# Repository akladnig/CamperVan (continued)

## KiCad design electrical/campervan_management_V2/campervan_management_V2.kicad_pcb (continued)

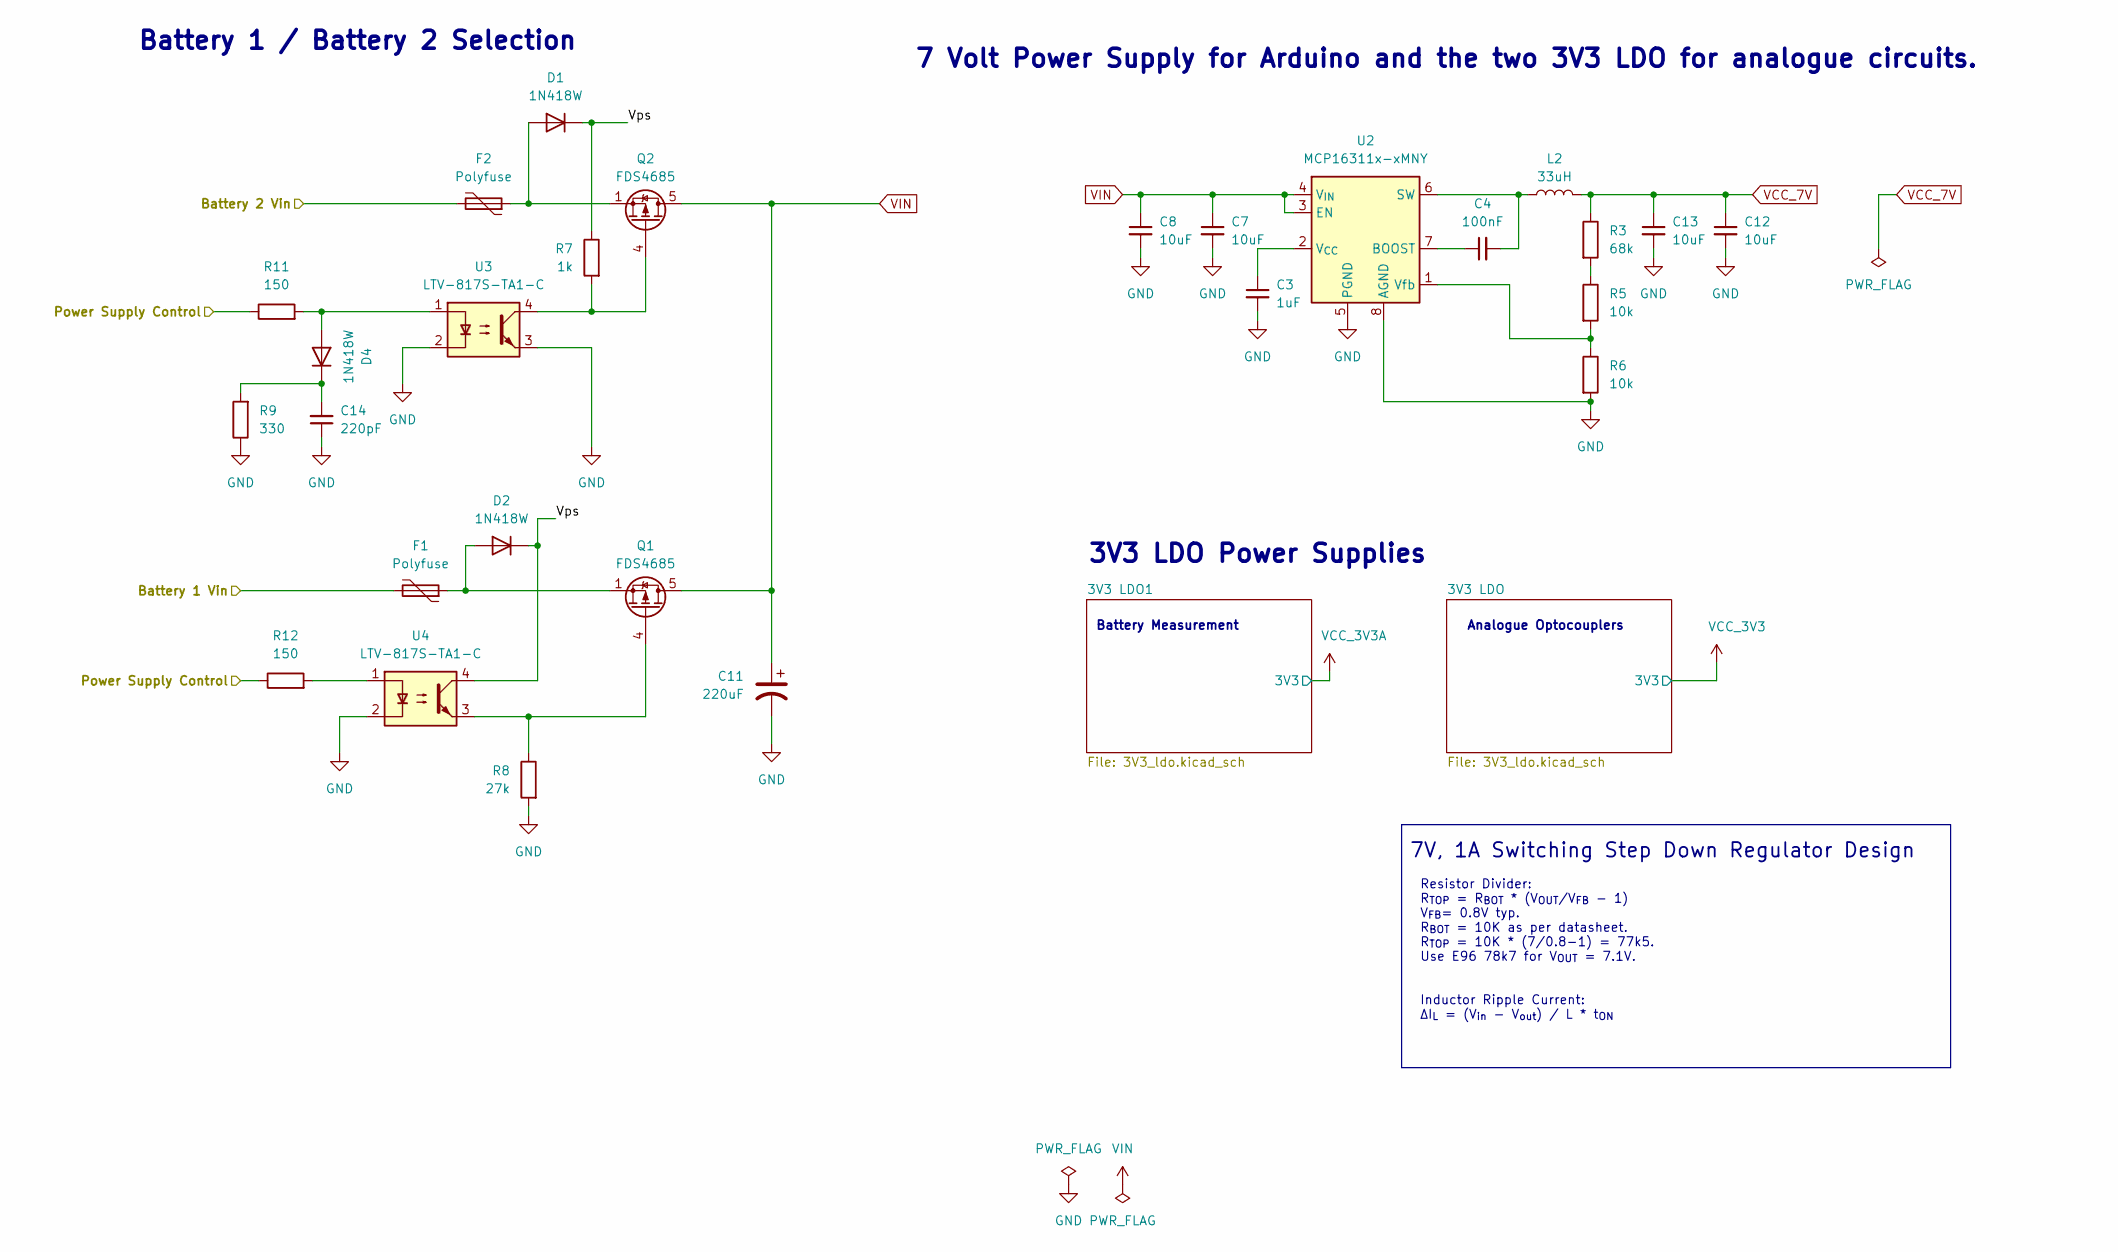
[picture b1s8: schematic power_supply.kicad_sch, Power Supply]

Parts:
C3: 1uF; C_0603_1608Metric; LCSC PN C15849
C4: 100nF; C_0805_2012Metric; LCSC PN C28233
C7, C8, C12, C13: 10uF; C_1206_3216Metric; LCSC PN C13585
C11: 220uF; C_Radial_D6.3mm_H11.0mm_P2.50mm
C14: 220pF; C_0805_2012Metric; LCSC PN C28233
D1, D2, D4: 1N418W; D_SOD-123; LCSC PN C81598
F1, F2: Polyfuse; Fuse_1812_4532Metric
L2: 33uH; L_Coilcraft_MSS1038-XXX; LCSC PN C19191679
Q1, Q2: FDS4685; SOIC-8_3.9x4.9mm_P1.27mm; LCSC PN C336026
R3: 68k; R_0603_1608Metric; LCSC PN C23231
R5, R6: 10k; R_0603_1608Metric; LCSC PN C25804
R7: 1k; R_0805_2012Metric; LCSC PN C17713
R8: 27k; R_0805_2012Metric; LCSC PN C17713
R9: 330; R_0805_2012Metric; LCSC PN C17471
R11, R12: 150; R_0805_2012Metric; LCSC PN C17471
U2: MCP16311x-xMNY; DFN-8-1EP_3x2mm_P0.5mm_EP1.75x1.45mm; LCSC PN C510882
U3, U4: LTV-817S-TA1-C; SO-4_4.4x3.6mm_P2.54mm; LCSC PN C109227

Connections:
/Battery Voltage Measurement/Battery 1 Vin: F2.2; also elsewhere on the board
/Battery Voltage Measurement/Battery 2 Vin: F1.2; also elsewhere on the board
/Power Supply Control: R11.1, R12.1; also elsewhere on the board
/Power Supply/Vps: D1.1 (K), D2.1 (K), R7.1, U4.4
GND: C3.2, C7.2, C8.2, C11.2, C12.2, C13.2, C14.1, R6.2, R8.2, R9.1, U2.5 (PGND), U2.8 (AGND), U2.9 (GND), U3.2, U3.3, U4.2; also elsewhere on the board
unnamed: D1.2 (A), F2.1, Q2.1 (S), Q2.2 (S), Q2.3 (S)
unnamed: D2.2 (A), F1.1, Q1.1 (S), Q1.2 (S), Q1.3 (S)
unnamed: D4.2 (A), R11.2, U3.1
unnamed: C14.2, D4.1 (K), R9.2
unnamed: Q1.4 (G), R8.1, U4.3
unnamed: Q2.4 (G), R7.2, U3.4
unnamed: R3.2, R5.1
unnamed: R12.2, U4.1
unnamed: C4.1, U2.7 (BOOST)
unnamed: C4.2, L2.1, U2.6 (SW)
unnamed: C3.1, U2.2 (V_{CC})
unnamed: R5.2, R6.1, U2.1 (Vfb)
VCC_7V: C12.1, C13.1, L2.2, R3.1; also elsewhere on the board
VIN: C7.1, C8.1, C11.1, Q1.5 (D), Q1.6 (D), Q1.7 (D), Q1.8 (D), Q2.5 (D), Q2.6 (D), Q2.7 (D), Q2.8 (D), U2.3 (EN), U2.4 (V_{IN}); also elsewhere on the board

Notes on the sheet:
7V, 1A Switching Step Down Regulator Design
Battery Measurement
Resistor Divider: R_{TOP} = R_{BOT} * (V_{OUT}/V_{FB} - 1) V_{FB}= 0.8V typ. R_{BOT} = 10K as per datasheet. R_{TOP} = 10K * (7/0.8-1) = 77k5. Use E96 78k7 for V_{OUT} = 7.1V. Inductor Ripple Current: ∆I_{L} = (V_{in} - V_{out}) / L * t_{ON}
3V3 LDO Power Supplies
Analogue Optocouplers
Battery 1 / Battery 2 Selection
7 Volt Power Supply for Arduino and the two 3V3 LDO for analogue circuits.

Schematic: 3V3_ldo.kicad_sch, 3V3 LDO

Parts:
C15: 1uF; C_0603_1608Metric; LCSC PN C15849
C17, C18: 10uF; CP_EIA-3216-18_Kemet-A; LCSC PN C7171
U5: AMS1117-3.3/TLV761; SOT-223-3_TabPin2; LCSC PN C6186

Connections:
GND: C15.2, C17.2, C18.2, U5.1 (GND); also elsewhere on the board
VCC_3V3: C17.1, C18.1, U5.2 (VO); also elsewhere on the board
VCC_7V: C15.1, U5.3 (VI); also elsewhere on the board

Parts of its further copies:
C36: 1uF; C_0603_1608Metric; LCSC PN C15849
C37, C38: 10uF; CP_EIA-3216-18_Kemet-A; LCSC PN C7171
U22: AMS1117-3.3/TLV761; SOT-223-3_TabPin2; LCSC PN C6186

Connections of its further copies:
GND: C36.2, C37.2, C38.2, U22.1 (GND); also elsewhere on the board
VCC_3V3A: C37.1, C38.1, U22.2 (VO); also elsewhere on the board
VCC_7V: C36.1, U22.3 (VI); also elsewhere on the board

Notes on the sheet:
3V3 LDO One is used to power the battery voltage measurement. The second for all other 3V3 devices.

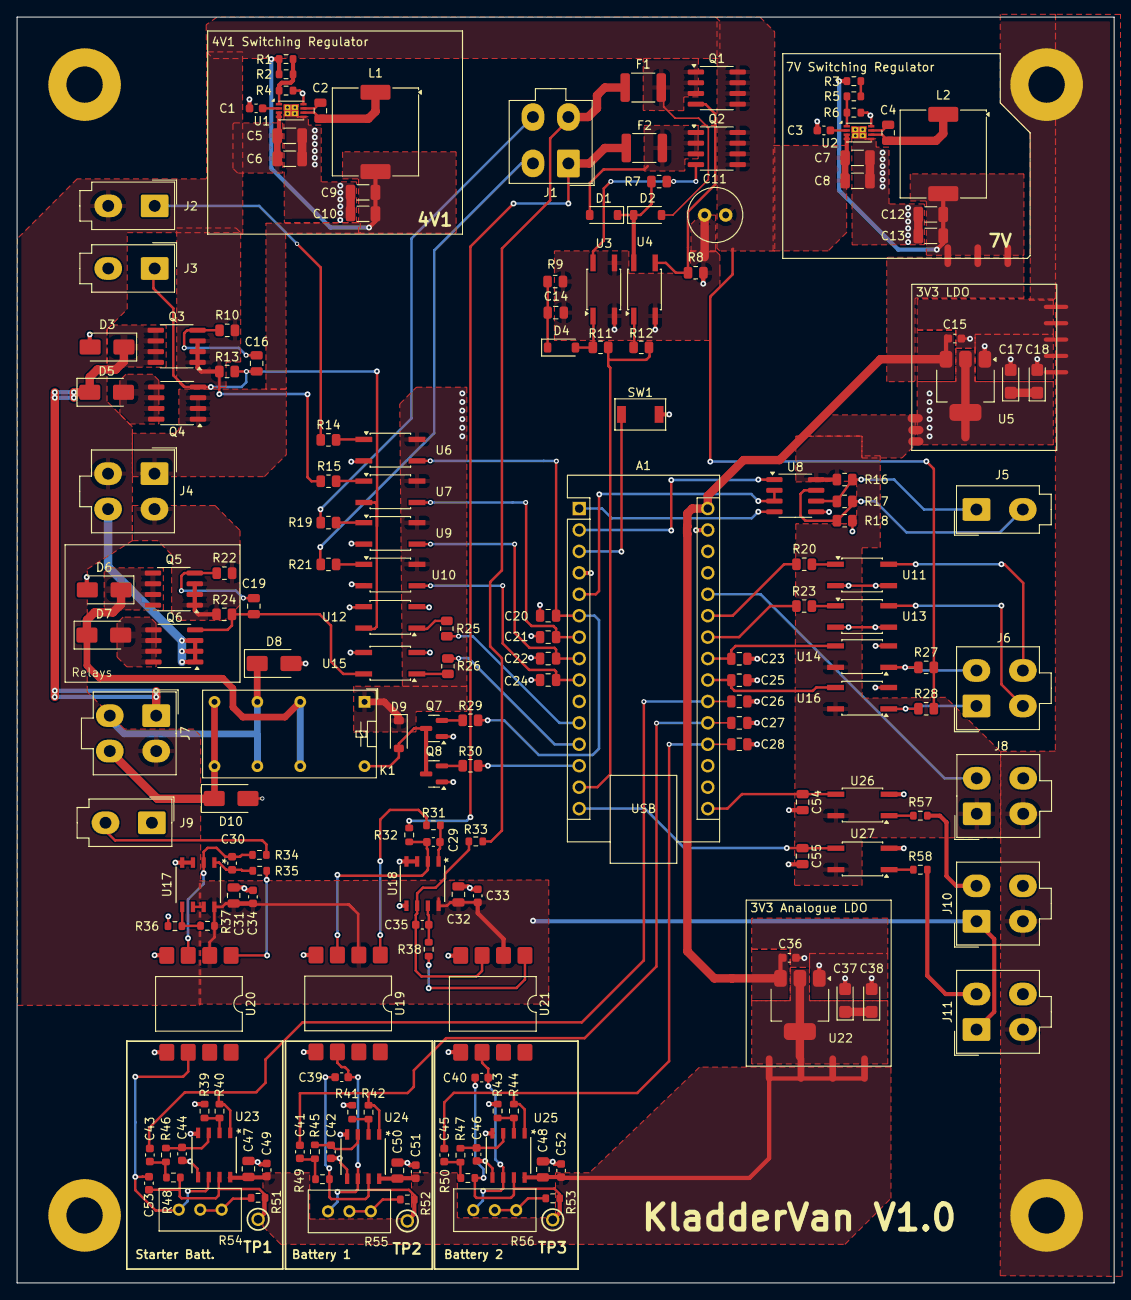
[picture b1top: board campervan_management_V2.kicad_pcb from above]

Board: 4 copper layers, 130.0 x 150.0 mm, 183 parts (0 on the bottom side), 113 nets.

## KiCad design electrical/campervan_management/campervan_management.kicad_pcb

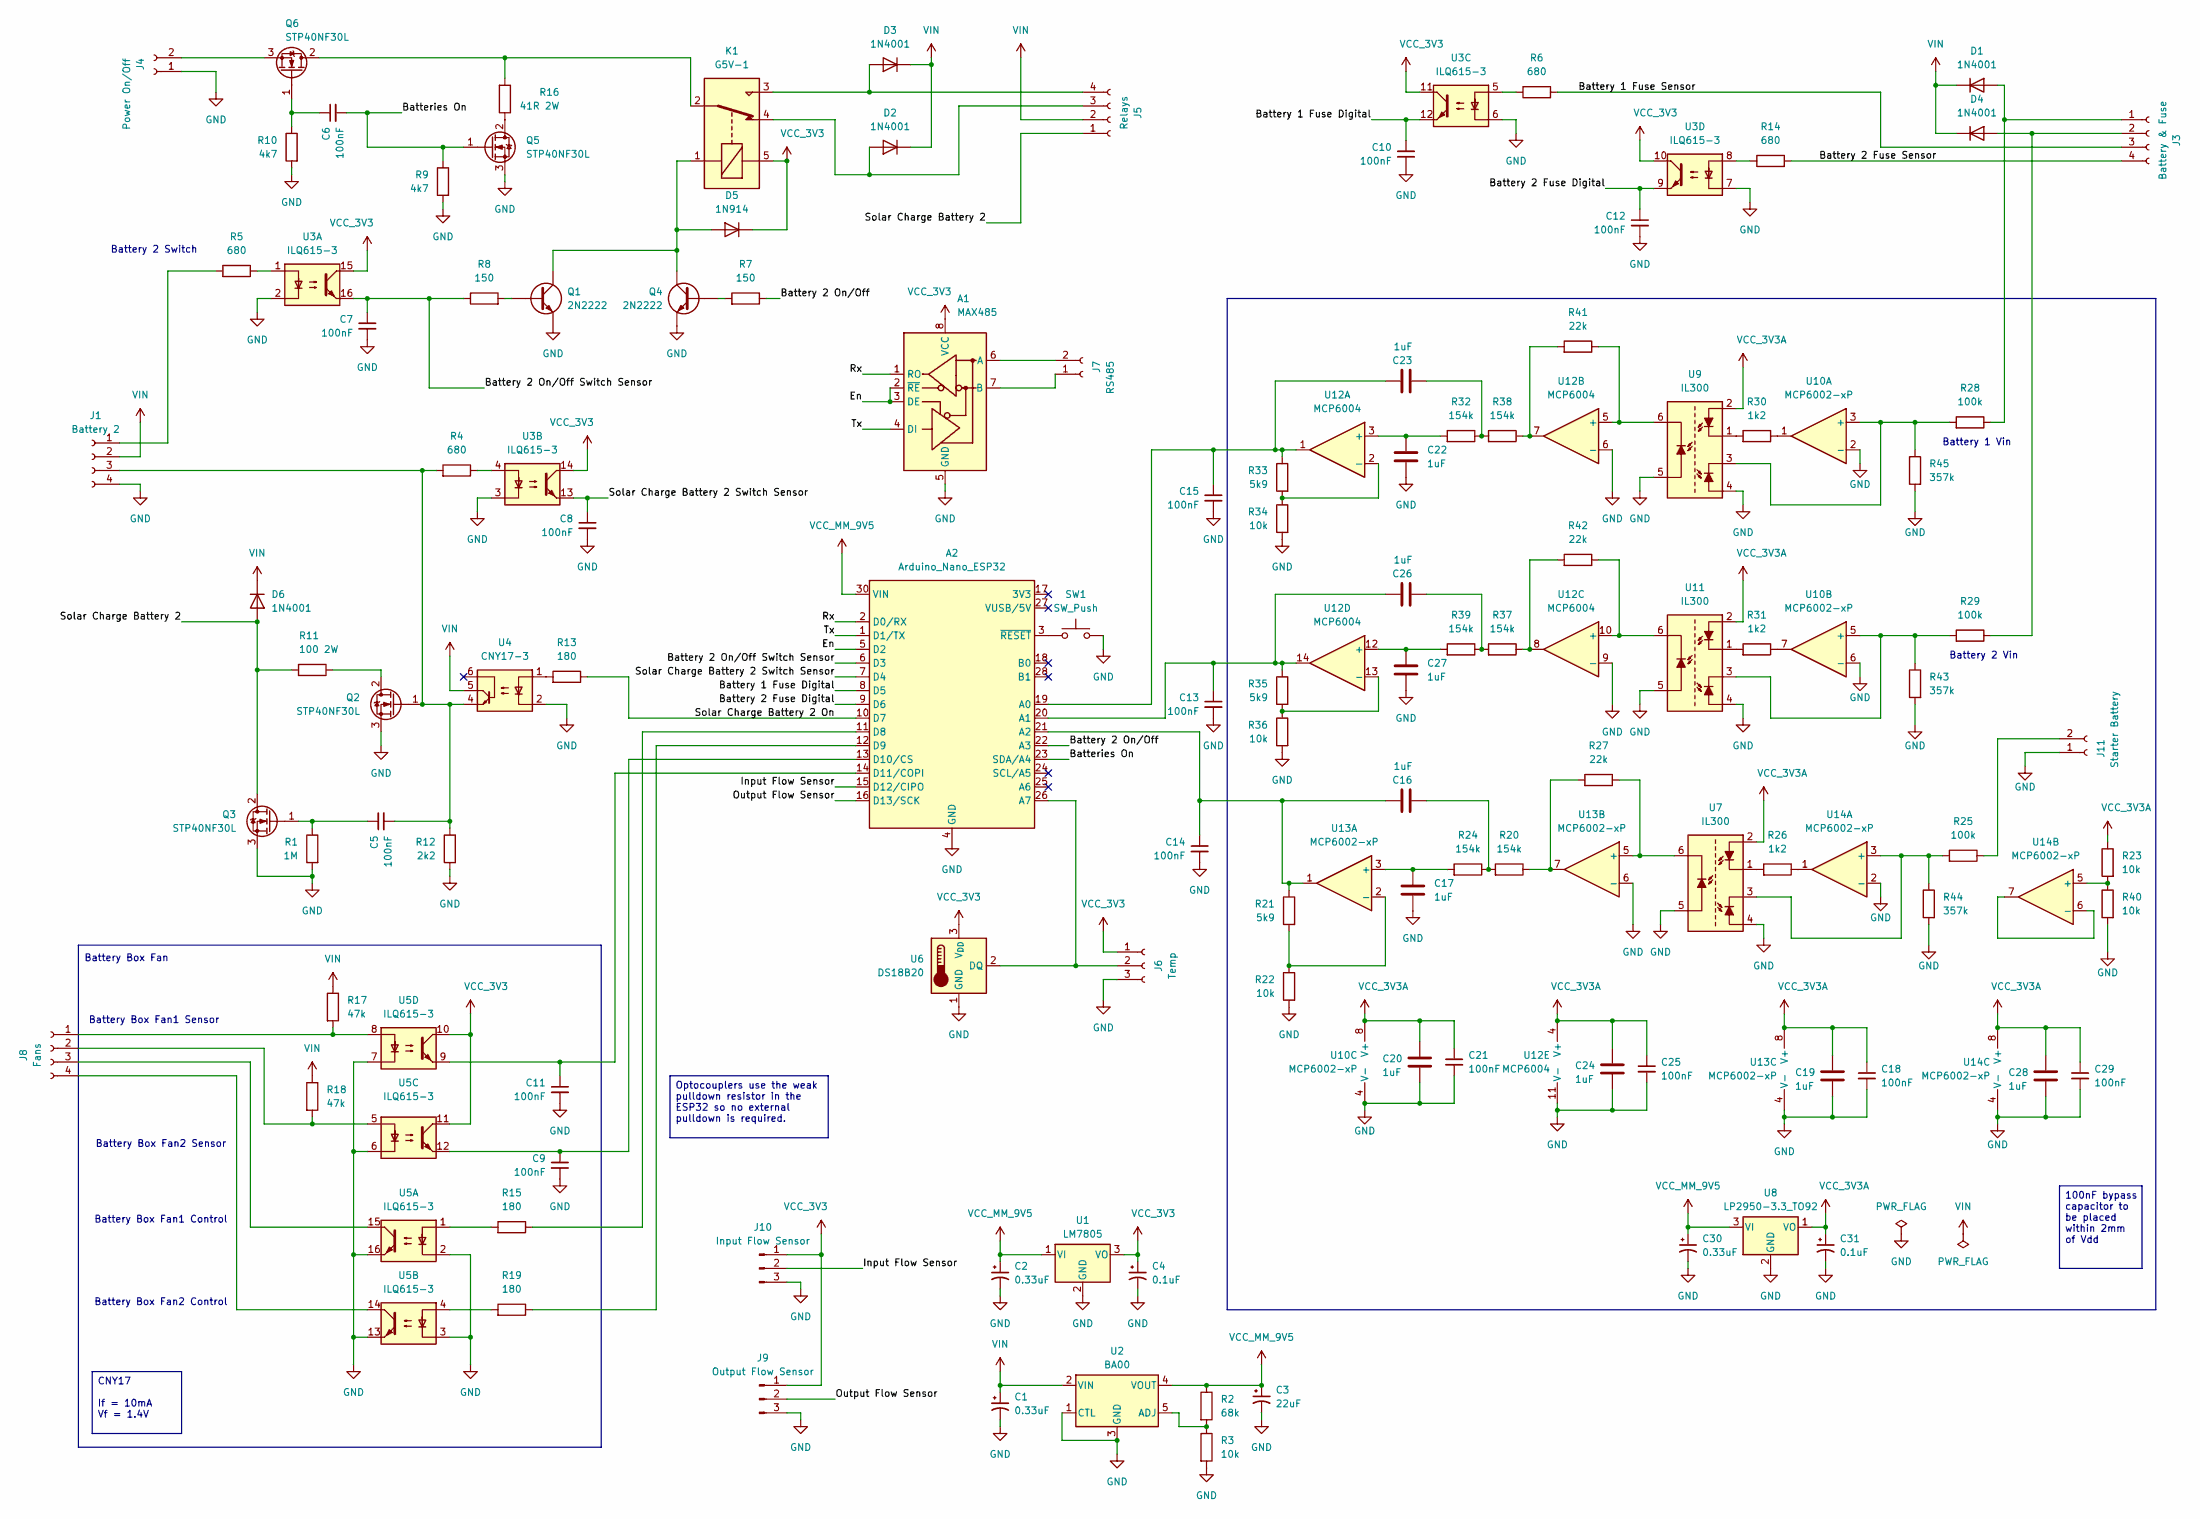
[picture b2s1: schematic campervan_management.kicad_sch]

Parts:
A1: MAX485; RS485_MODULE
A2: Arduino_Nano_ESP32; Arduino_Nano
C1, C2, C30: 0.33uF; C_Disc_D5.0mm_W2.5mm_P2.50mm
C3: 22uF; CP_Radial_Tantal_D4.5mm_P2.50mm
C4, C31: 0.1uF; CP_Radial_Tantal_D5.0mm_P5.00mm
C5, C6, C7, C8, C9, C10, C11, C12, C13, C14, C15, C18, C21, C25, C29: 100nF; C_Disc_D3.8mm_W2.6mm_P2.50mm
C16, C17, C19, C20, C22, C23, C24, C26, C27, C28: 1uF; CAP_NP_5X11_MTC
D1, D2, D3, D4, D6: 1N4001; D_DO-41_SOD81_P10.16mm_Horizontal
D5: 1N914; D_DO-35_SOD27_P7.62mm_Horizontal
J1: Battery 2; Molex_Mini-Fit_Jr_5566-04A_2x02_P4.20mm_Vertical
J3: Battery & Fuse; Molex_Mini-Fit_Jr_5566-04A_2x02_P4.20mm_Vertical
J4: Power On/Off; Molex_Mini-Fit_Jr_5566-02A_2x01_P4.20mm_Vertical
J5: Relays; Molex_Mini-Fit_Jr_5566-04A_2x02_P4.20mm_Vertical
J6: Temp; PinSocket_1x03_P2.54mm_Vertical
J7: RS485; Molex_Mini-Fit_Jr_5566-02A_2x01_P4.20mm_Vertical
J8: Fans; Molex_Mini-Fit_Jr_5566-04A_2x02_P4.20mm_Vertical
J9: Output Flow Sensor; PinSocket_1x03_P2.54mm_Vertical
J10: Input Flow Sensor; PinSocket_1x03_P2.54mm_Vertical
J11: Starter Battery; Molex_Mini-Fit_Jr_5566-02A_2x01_P4.20mm_Vertical
K1: G5V-1; Relay_SPDT_Omron-G5Q-1
Q1, Q4: 2N2222; TO-18-3
Q2, Q3, Q5, Q6: STP40NF30L; TO-220F-3_Vertical
R1: 1M; R_Axial_DIN0207_L6.3mm_D2.5mm_P10.16mm_Horizontal
R2: 68k; R_Axial_DIN0207_L6.3mm_D2.5mm_P10.16mm_Horizontal
R3, R22, R23, R34, R36, R40: 10k; R_Axial_DIN0207_L6.3mm_D2.5mm_P10.16mm_Horizontal
R4, R5, R6, R14: 680; R_Axial_DIN0207_L6.3mm_D2.5mm_P10.16mm_Horizontal
R7, R8: 150; R_Axial_DIN0207_L6.3mm_D2.5mm_P10.16mm_Horizontal
R9, R10: 4k7; R_Axial_DIN0207_L6.3mm_D2.5mm_P10.16mm_Horizontal
R11: 100 2W; R_Axial_DIN0414_L11.9mm_D4.5mm_P25.40mm_Horizontal
R12: 2k2; R_Axial_DIN0207_L6.3mm_D2.5mm_P10.16mm_Horizontal
R13, R15, R19: 180; R_Axial_DIN0207_L6.3mm_D2.5mm_P10.16mm_Horizontal
R16: 41R 2W; R_Axial_DIN0414_L11.9mm_D4.5mm_P25.40mm_Horizontal
R17, R18: 47k; R_Axial_DIN0207_L6.3mm_D2.5mm_P10.16mm_Horizontal
R20, R24, R32, R37, R38, R39: 154k; R_Axial_DIN0207_L6.3mm_D2.5mm_P10.16mm_Horizontal
R21, R33, R35: 5k9; R_Axial_DIN0207_L6.3mm_D2.5mm_P10.16mm_Horizontal
R25, R28, R29: 100k; R_Axial_DIN0207_L6.3mm_D2.5mm_P10.16mm_Horizontal
R26, R30, R31: 1k2; R_Axial_DIN0207_L6.3mm_D2.5mm_P10.16mm_Horizontal
R27, R41, R42: 22k; R_Axial_DIN0207_L6.3mm_D2.5mm_P10.16mm_Horizontal
R43, R44, R45: 357k; R_Axial_DIN0207_L6.3mm_D2.5mm_P10.16mm_Horizontal
SW1: SW_Push; SW_TH_Tactile_Omron_B3F-102x
U1: LM7805; TO-220-3_Vertical
U2: BA00; TO-220-5_P3.4x3.8mm_StaggerOdd_Lead7.13mm_TabDown
U3, U5: ILQ615-3; DIP-16_W7.62mm
U4: CNY17-3; DIP-6_W7.62mm
U6: DS18B20; TO-92_Inline
U7, U9, U11: IL300; DIP-8_W7.62mm
U8: LP2950-3.3_TO92; TO-92_Inline
U10, U13, U14: MCP6002-xP; DIP-8_W7.62mm
U12: MCP6004; DIP-14_W7.62mm

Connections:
/Batteries On: A2.23 (SDA/A4), C6.2, Q5.1 (G), R9.1
/Battery 1 Fuse Digital: A2.8 (D5), C10.1, U3.12
/Battery 1 Fuse Sensor: J3.3, R6.2
/Battery 2 Fuse Digital: A2.9 (D6), C12.1, U3.9
/Battery 2 Fuse Sensor: J3.4, R14.2
/Battery 2 On/Off: A2.22 (A3), R7.1
/Battery 2 On/Off Switch Sensor: A2.6 (D3), C7.1, R8.1, U3.16
/En: A1.2 (~RE), A1.3 (DE), A2.5 (D2)
/Input Flow Sensor: A2.15 (D12/CIPO), J10.2
/Output Flow Sensor: A2.16 (D13/SCK), J9.2
/Rx: A1.1 (RO), A2.2 (D0/RX)
/Solar Charge Battery 2: D6.2 (A), J5.1, Q3.2 (D), R11.2
/Solar Charge Battery 2 On: A2.10 (D7), R13.1
/Solar Charge Battery 2 Switch Sensor: A2.7 (D4), C8.1, U3.13
/Tx: A1.4 (DI), A2.1 (D1/TX)
GND: A1.5 (GND), A2.4 (GND), A2.29 (GND), C1.2, C2.2, C3.2, C4.2, C7.2, C8.2, C9.2, C10.2, C11.2, C12.2, C13.2, C14.2, C15.2, C17.2, C18.2, C19.2, C20.2, C21.2, C22.2, C24.2, C25.2, C27.2, C28.2, C29.2, C30.2, C31.2, J1.4, J4.1, J6.3, J9.3, J10.3, J11.1, Q1.1 (E), Q2.3 (S), Q3.3 (S), Q4.1 (E), Q5.3 (S), R1.2, R3.2, R9.2, R10.2, R12.2, R22.2, R34.2, R36.2, R40.2, R43.2, R44.2, R45.2, SW1.2, U1.2 (GND), U2.1 (CTL), U2.3 (GND), U3.2, U3.3, U3.6, U3.7, U4.2, U5.2, U5.3, U5.6, U5.7, U5.13, U5.16, U6.1 (GND), U7.4, U7.5, U8.2 (GND), U9.4, U9.5, U10.2 (-), U10.4 (V-), U10.6 (-), U11.4, U11.5, U12.6 (-), U12.9 (-), U12.11 (V-), U13.4 (V-), U13.6 (-), U14.2 (-), U14.4 (V-)
unnamed: A1.6 (A), J7.2
unnamed: A1.7 (B), J7.1
unnamed: A2.19 (A0), C15.1, C23.2, R33.1, U12.1
unnamed: A2.20 (A1), C13.1, C26.2, R35.1, U12.14
unnamed: A2.21 (A2), C14.1, C16.2, R21.1, U13.1
unnamed: A2.26 (A7), J6.2, U6.2 (DQ)
unnamed: A2.11 (D8), R15.1
unnamed: A2.12 (D9), R19.1
unnamed: A2.13 (D10/CS), C9.1, U5.12
unnamed: A2.14 (D11/COPI), C11.1, U5.9
unnamed: A2.3 (~RESET), SW1.1
unnamed: C16.1, R20.2, R24.1
unnamed: C23.1, R32.1, R38.2
unnamed: C26.1, R37.2, R39.1
unnamed: D1.2 (A), J3.1, R28.1
unnamed: D2.2 (A), J5.3, K1.4
unnamed: D3.2 (A), J5.4, K1.3
unnamed: D4.2 (A), J3.2, R29.1
unnamed: D5.2 (A), K1.1, Q1.3 (C), Q4.3 (C)
unnamed: J1.1, R5.2
unnamed: C5.2, J1.3, Q2.1 (G), R4.2, R12.1, U4.4
unnamed: J4.2, Q6.3 (S)
unnamed: J8.1, R17.2, U5.8
unnamed: J8.2, R18.2, U5.5
unnamed: J8.3, U5.15
unnamed: J8.4, U5.14
unnamed: J11.2, R25.1
unnamed: Q1.2 (B), R8.2
unnamed: Q2.2 (D), R11.1
unnamed: C5.1, Q3.1 (G), R1.1
unnamed: Q4.2 (B), R7.2
unnamed: Q5.2 (D), R16.1
unnamed: K1.2, Q6.2 (D), R16.2
unnamed: C6.1, Q6.1 (G), R10.1
unnamed: R4.1, U3.4
unnamed: R5.1, U3.1
unnamed: R6.1, U3.5
unnamed: R13.2, U4.1
unnamed: R14.1, U3.8
unnamed: R15.2, U5.1
unnamed: R19.2, U5.4
unnamed: R20.1, R27.2, U13.7
unnamed: R26.1, U14.1
unnamed: R26.2, U7.1
unnamed: R30.1, U10.1
unnamed: R30.2, U9.1
unnamed: R31.1, U10.7
unnamed: R31.2, U11.1
unnamed: R37.1, R42.2, U12.8
unnamed: R38.1, R41.2, U12.7
unnamed: R2.2, R3.1, U2.5 (ADJ)
unnamed: R28.2, R45.1, U9.3, U10.3 (+)
unnamed: R29.2, R43.1, U10.5 (+), U11.3
unnamed: C22.1, R32.2, U12.3 (+)
unnamed: R33.2, R34.1, U12.2 (-)
unnamed: R41.1, U9.6, U12.5 (+)
unnamed: R42.1, U11.6, U12.10 (+)
unnamed: C27.1, R39.2, U12.12 (+)
unnamed: R35.2, R36.1, U12.13 (-)
unnamed: C17.1, R24.2, U13.3 (+)
unnamed: R21.2, R22.1, U13.2 (-)
unnamed: R27.1, U7.6, U13.5 (+)
unnamed: R25.2, R44.1, U7.3, U14.3 (+)
unnamed: R23.2, R40.1, U14.5 (+)
unnamed: U14.6 (-), U14.7
VCC_3V3: A1.8 (VCC), C4.1, D5.1 (K), J6.1, J9.1, J10.1, K1.5, U1.3 (VO), U3.10, U3.11, U3.14, U3.15, U5.10, U5.11, U6.3 (V_{DD})
VCC_3V3A: C18.1, C19.1, C20.1, C21.1, C24.1, C25.1, C28.1, C29.1, C31.1, R23.1, U7.2, U8.1 (VO), U9.2, U10.8 (V+), U11.2, U12.4 (V+), U13.8 (V+), U14.8 (V+)
VCC_MM_9V5: A2.30 (VIN), C2.1, C3.1, C30.1, R2.1, U1.1 (VI), U2.4 (VOUT), U8.3 (VI)
VIN: C1.1, D1.1 (K), D2.1 (K), D3.1 (K), D4.1 (K), D6.1 (K), J1.2, J5.2, R17.1, R18.1, U2.2 (VIN), U4.5

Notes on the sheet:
Battery Box Fan
Battery 2 Switch
Battery Box Fan1 Control
Battery 2 Vin
Battery Box Fan1 Sensor
Battery Box Fan2 Sensor
Battery Box Fan2 Control
Battery 1 Vin
Optocouplers use the weak pulldown resistor in the ESP32 so no external pulldown is required.
CNY17 If = 10mA Vf = 1.4V
100nF bypass capacitor to be placed within 2mm of Vdd

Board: 2 copper layers, 116 parts (0 on the bottom side), 85 nets, no tracks yet.

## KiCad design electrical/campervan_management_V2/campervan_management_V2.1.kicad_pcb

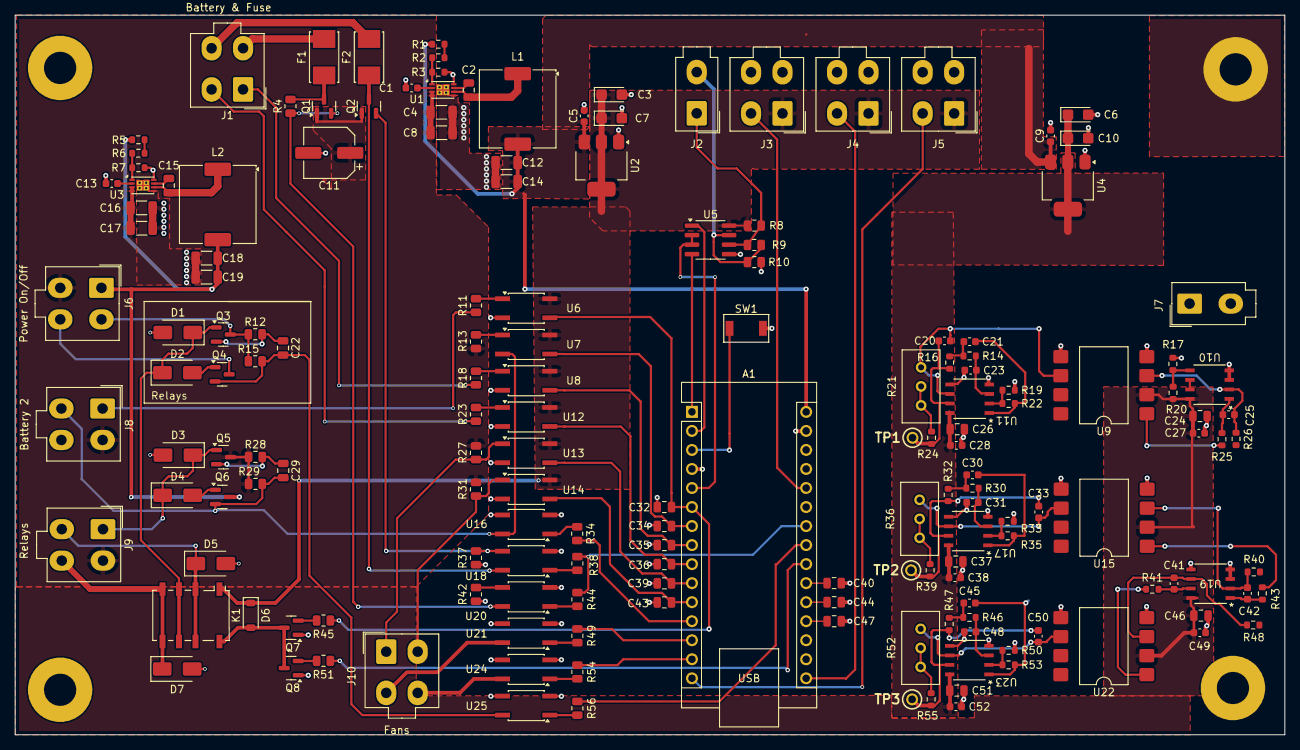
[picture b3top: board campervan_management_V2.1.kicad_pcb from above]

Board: 4 copper layers, 169.5 x 96.0 mm, 172 parts (0 on the bottom side), 109 nets.

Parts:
A1: Arduino_Nano_ESP32; Arduino_Nano
C1, C5, C9, C13, C21, C23, C27, C28, C30, C31, C38, C45, C48, C49, C52: 1uF; C_0603_1608Metric
C2, C15, C22, C24, C26, C29, C32, C34, C35, C36, C37, C39, C40, C43, C44, C46, C47, C51: 100nF; C_0805_2012Metric
C3, C6, C7, C10: 10uF; CP_EIA-3216-18_Kemet-A
C4, C8, C12, C14, C16, C17, C18, C19: 10uF; C_1206_3216Metric
C11: 220uF; CP_Elec_6.3x5.9
C20, C25, C33, C41, C42, C50: C_Small; C_0603_1608Metric
D1, D2, D3, D4, D5, D7: M7; D_SMA
D6: 1N418W; D_SOD-123
F1, F2: Polyfuse; Fuseholder_Littelfuse_Nano2_157x
H1, H2, H3, H4: MountingHole_Pad; MountingHole_4.3mm_M4_Pad
J1: Battery & Fuse; Molex_Mini-Fit_Jr_5566-04A_2x02_P4.20mm_Vertical
J2: RS485; Molex_Mini-Fit_Jr_5566-02A_2x01_P4.20mm_Vertical
J3: Temp; Molex_Mini-Fit_Jr_5566-04A_2x02_P4.20mm_Vertical
J4: Output Flow Sensor; Molex_Mini-Fit_Jr_5566-04A_2x02_P4.20mm_Vertical
J5: Input Flow Sensor; Molex_Mini-Fit_Jr_5566-04A_2x02_P4.20mm_Vertical
J6: Power On/Off Switch; Molex_Mini-Fit_Jr_5566-04A_2x02_P4.20mm_Vertical
J7: Starter Battery; Molex_Mini-Fit_Jr_5566-02A_2x01_P4.20mm_Vertical
J8: Battery 2; Molex_Mini-Fit_Jr_5566-04A_2x02_P4.20mm_Vertical
J9: Relays; Molex_Mini-Fit_Jr_5566-04A_2x02_P4.20mm_Vertical
J10: Fans; Molex_Mini-Fit_Jr_5566-04A_2x02_P4.20mm_Vertical
K1: G6KU-2; Relay_DPDT_Omron_G6K-2F-Y
L1: 33uH; L_Coilcraft_MSS1038-XXX
L2: 18uH; L_Coilcraft_MSS1038-XXX
Q1, Q2, Q3, Q4, Q5, Q6: Q_PMOS_DGS; SOT-23
Q7, Q8: MMBT2222A; SOT-23
R1, R5: 68k; R_0603_1608Metric
R2, R3, R6, R7, R17, R19, R20, R33, R50: 10k; R_0603_1608Metric
R4, R15, R27, R29, R31, R37, R42: 47k; R_0805_2012Metric
R8, R10: 931; R_0805_2012Metric
R9: 120; R_0805_2012Metric
R11, R13, R18, R23: 680; R_0805_2012Metric
R12, R28: 1M; R_0805_2012Metric
R14, R16, R30, R32, R46, R47: 150k; R_0603_1608Metric
R21, R36, R52: 10k; Potentiometer_Bourns_3296W_Vertical
R22, R35, R53: 5k6; R_0603_1608Metric
R24, R39, R55: 22k; R_0603_1608Metric
R25, R41, R43: 1k2; R_0603_1608Metric
R26, R40, R48: 220k; R_0603_1608Metric
R34, R38, R44, R45, R49, R51, R54, R56: 150; R_0805_2012Metric
SW1: SW_Push; SW_SPST_JLC
TP1, TP2, TP3: TestPoint; 5000
U1, U3: MCP16311x-xMNY; DFN-8-1EP_3x2mm_P0.5mm_EP1.75x1.45mm
U2, U4: AMS1117-3.3; SOT-223-3_TabPin2
U5: MAX487E; SOIC-8_3.9x4.9mm_P1.27mm
U6, U7, U8, U12, U13, U14, U16, U18, U20, U21, U24, U25: LTV-817S-TA1-C; SO-4_4.4x3.6mm_P2.54mm
U9, U15, U22: HCNR200-500E; SMDIP-8_W11.48mm
U10, U11, U17, U19, U23: LM358DR2G; SOIC-8_ONS-L

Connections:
/Batteries On: A1.23 (SDA/A4), R56.1
/Battery 1 Fuse State: A1.8 (D5), C35.1, U8.3
/Battery 2 Fuse State: A1.9 (D6), C36.1, U12.3
/Battery 2 On/Off: A1.22 (A3), R51.1
/Battery 2 On/Off Switch Sensor: A1.6 (D3), C32.1, R45.1, U6.3
/Battery Box Fan1 Control: A1.13 (D10/CS), R49.1
/Battery Box Fan1 Sensor: A1.11 (D8), C43.1, U14.3
/Battery Box Fan2 Control: A1.14 (D11/COPI), R54.1
/Battery Box Fan2 Sensor: A1.10 (D7), C39.1, U13.3
/Battery Fuse Sensors/Battery 1 Fuse Sensor: J1.1, R18.2
/Battery Fuse Sensors/Battery 2 Fuse Sensor: J1.2, R23.2
/Battery Management/Battery 1 Relay: D7.1 (K), J9.4, K1.4, K1.5
/Battery Management/Battery 2 Relay: D5.1 (K), J9.3, K1.2, K1.7
/Battery Management/Battery 2 Switch: J8.1, R11.2
/Battery Management/Power On Switch - 4V1: J6.2, Q3.3 (S), R12.1, R15.1
/Battery Management/Power On Switch - Vin: J6.4, Q4.3 (S)
/Battery Voltage Measurement/Battery 1 Vin: F2.2, J1.4, R40.1
/Battery Voltage Measurement/Battery 1 Voltage: A1.20 (A1), C30.2, C44.1, R35.1, U17.1
/Battery Voltage Measurement/Battery 2 Vin: F1.2, J1.3, R48.1
/Battery Voltage Measurement/Battery 2 Voltage: A1.21 (A2), C40.1, C45.2, R53.1, U23.1
/Battery Voltage Measurement/Starter Battery Vin: J7.2, R26.1
/Battery Voltage Measurement/Starter Battery Voltage: A1.19 (A0), C21.2, C47.1, R22.1, U11.1
/En: A1.5 (D2), U5.2 (~RE), U5.3 (DE)
/Input Flow Sensor: A1.15 (D12/CIPO), J5.2
/Output Flow Sensor: A1.16 (D13/SCK), J4.2
/Power Supply Control: A1.24 (SCL/A5), R38.1, R44.1
/Rx: A1.2 (D0/RX), U5.1 (RO)
/Solar Charge Battery 2 Relay: D3.1 (K), D4.1 (K), J9.1, Q5.1 (D)
/Solar Charge Management/Solar Charge Battery 2 On: A1.12 (D9), R34.1
/Solar Charge Management/Solar Charge Battery 2 Switch: C29.2, J8.3, Q6.2 (G), R29.2, U7.2, U16.4
/Solar Charge Management/Solar Charge Battery 2 Switch Sensor: A1.7 (D4), C34.1, U7.3
/Tx: A1.1 (D1/TX), U5.4 (DI)
GND: A1.4 (GND), A1.29 (GND), C1.2, C3.2, C4.2, C5.2, C6.2, C7.2, C8.2, C9.2, C10.2, C11.2, C12.2, C13.2, C14.2, C16.2, C17.2, C18.2, C19.2, C23.2, C24.2, C26.2, C27.2, C28.2, C31.2, C32.2, C34.2, C35.2, C36.2, C37.2, C38.2, C39.2, C40.2, C43.2, C44.2, C46.2, C47.2, C48.2, C49.2, C51.2, C52.2, D1.2 (A), D3.2 (A), D5.2 (A), D7.2 (A), H1.1, H2.1, H3.1, H4.1, J3.3, J4.3, J5.3, J7.1, J8.4, Q7.1 (E), Q8.1 (E), R3.2, R7.2, R10.2, R17.2, R19.2, R33.2, R37.2, R42.2, R50.2, SW1.2, U1.5 (PGND), U1.8 (AGND), U1.9 (GND), U2.1 (GND), U3.5 (PGND), U3.8 (AGND), U3.9 (GND), U4.1 (GND), U5.5 (GND), U6.2, U8.2, U9.4, U9.5, U10.3 (+), U10.4 (V-), U11.4 (V-), U11.5 (+), U12.2, U13.2, U14.2, U15.4, U15.5, U16.2, U16.3, U17.4 (V-), U17.5 (+), U18.2, U19.3 (+), U19.4 (V-), U19.5 (+), U20.2, U21.2, U21.3, U22.4, U22.5, U23.4 (V-), U23.5 (+), U24.2, U24.3, U25.2, U25.3
unnamed: A1.26 (A7), J3.2
unnamed: A1.3 (~RESET), SW1.1
unnamed: C25.1, R25.1, U10.1
unnamed: C20.1, R16.1, R24.2, TP1.1, U11.7
unnamed: C41.1, R41.1, U19.7
unnamed: C45.1, R46.1, R47.2
unnamed: C30.1, R30.1, R32.2
unnamed: C21.1, R14.1, R16.2
unnamed: C42.1, R43.1, U19.1
unnamed: C50.1, R47.1, R55.2, TP3.1, U23.7
unnamed: C33.1, R32.1, R39.2, TP2.1, U17.7
unnamed: D4.2 (A), Q6.1 (D)
unnamed: D2.2 (A), Q4.1 (D)
unnamed: D1.1 (K), D2.1 (K), K1.3, K1.6, Q3.1 (D)
unnamed: D6.2 (A), K1.8, Q7.3 (C), Q8.3 (C)
unnamed: J10.1, R27.2, U13.1
unnamed: J10.2, R31.2, U14.1
unnamed: J10.3, U21.4
unnamed: J10.4, U24.4
unnamed: J2.1, R8.2, R9.1, U5.6 (A)
unnamed: J2.2, R9.2, R10.1, U5.7 (B)
unnamed: C22.2, Q4.2 (G), R15.2, U25.4
unnamed: C22.1, Q3.2 (G), R12.2
unnamed: Q7.2 (B), R45.2
unnamed: Q8.2 (B), R51.2
unnamed: C29.1, Q5.2 (G), R28.2
unnamed: Q2.2 (G), R37.1, U18.3
unnamed: F2.1, Q2.3 (S), U18.4
unnamed: Q1.2 (G), R4.2, U20.4
unnamed: F1.1, Q1.3 (S), R4.1
unnamed: R1.2, R2.1
unnamed: R43.2, U15.1
unnamed: R41.2, U22.1
unnamed: R5.2, R6.1
unnamed: R52.1, R52.2, R55.1
unnamed: R34.2, U16.1
unnamed: R36.1, R36.2, R39.1
unnamed: R56.2, U25.1
unnamed: R13.2, U7.1
unnamed: R11.1, U6.1
unnamed: R25.2, U9.1
unnamed: R18.1, U8.1
unnamed: R21.1, R21.2, R24.1
unnamed: R23.1, U12.1
unnamed: R54.2, U24.1
unnamed: R49.2, U21.1
unnamed: R44.2, U20.1
unnamed: R42.1, U20.3
unnamed: R38.2, U18.1
unnamed: C2.1, U1.7 (BOOST)
unnamed: C2.2, L1.1, U1.6 (SW)
unnamed: C1.1, U1.2 (V_{CC})
unnamed: R2.2, R3.1, U1.1 (Vfb)
unnamed: C48.1, R46.2, U23.3 (+)
unnamed: R50.1, R53.2, U23.2 (-)
unnamed: C50.2, R52.3, U22.6, U23.6 (-)
unnamed: C42.2, R40.2, U15.3, U19.2 (-)
unnamed: C41.2, R48.2, U19.6 (-), U22.3
unnamed: C31.1, R30.2, U17.3 (+)
unnamed: R33.1, R35.2, U17.2 (-)
unnamed: C33.2, R36.3, U15.6, U17.6 (-)
unnamed: C25.2, R26.2, U9.3, U10.2 (-)
unnamed: R17.1, R20.2, U10.5 (+)
unnamed: U10.6 (-), U10.7
unnamed: C23.1, R14.2, U11.3 (+)
unnamed: R19.1, R22.2, U11.2 (-)
unnamed: C20.2, R21.3, U9.6, U11.6 (-)
unnamed: C15.1, U3.7 (BOOST)
unnamed: C15.2, L2.1, U3.6 (SW)
unnamed: C13.1, U3.2 (V_{CC})
unnamed: R6.2, R7.1, U3.1 (Vfb)
VCC_3V3: C3.1, C7.1, D6.1 (K), J3.1, J4.1, J5.1, K1.1, R8.1, U2.2 (VO), U5.8 (VCC), U6.4, U7.4, U8.4, U12.4, U13.4, U14.4
VCC_3V3A: C6.1, C10.1, C26.1, C28.1, C37.1, C38.1, C51.1, C52.1, U4.2 (VO), U11.8 (V+), U17.8 (V+), U23.8 (V+)
VCC_4V1: C18.1, C19.1, J6.1, L2.2, Q6.3 (S), R5.1
VCC_7V: A1.30 (VIN), C5.1, C9.1, C12.1, C14.1, L1.2, R1.1, U2.3 (VI), U4.3 (VI)
VIN: C4.1, C8.1, C11.1, C16.1, C17.1, C24.1, C27.1, C46.1, C49.1, J6.3, J8.2, J9.2, Q1.1 (D), Q2.1 (D), Q5.3 (S), R13.1, R20.1, R27.1, R28.1, R29.1, R31.1, U1.3 (EN), U1.4 (V_{IN}), U3.3 (EN), U3.4 (V_{IN}), U9.2, U10.8 (V+), U15.2, U19.8 (V+), U22.2

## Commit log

2025-04-06 second commit
2025-04-10 3rd commit
2025-04-16 4th commit
2025-04-16 Added design comments
2025-04-16 added schematic
2025-04-18 changed folder
2025-04-18 Added flow sensors and RS485
2025-04-18 updated electrical details
2025-04-18 removed RS485 TODO
2025-05-22 fix typos
2025-05-22 more typos!
2025-05-22 adjust size
2025-05-22 resize image
2025-05-22 fix formatting
2025-05-22 Updated TOC
2025-05-23 Design has been split into 3x modules
    - management module
    - fuse and switch modules
    - display module
2025-08-01 added infill to use wheelarch void
2025-08-01 added dimension for pop top
2025-08-01 added custom mattress size and increased size of headboaerd box to accomodate donna
2025-08-01 added handle to airfryer
2025-08-01 major updates to use a long box and changes to ducting
2025-08-01 changed water tank size and lowered bench height to allow window to be fitted
2025-08-01 added window, changed battery box, added parameter to show headboard box
2025-08-01 added pop top clearance and changed shelf height to support inverter
2025-08-01 added linear opto coupler design
2025-08-01 datasheets for selected components
2025-08-01 lots of redesign
2025-08-01 updated progress of todo
2025-08-01 changed benchheight to accomodate window
2025-08-01 added cupboard base panel
2025-08-01 formatting
2025-08-02 added showDimensions for draw front panels
2025-08-02 changed text size
2025-08-02 moved table design from cabinets to new file
2025-08-02 moved table design to new file
2025-08-02 changing clearances to see if sliding doors will work
2025-08-02 moved draw design to a separate file
2025-08-02 split cupboards into two separate modules
2025-08-03 split cupboards into modules and added openDrawsAndDoors parameter
2025-08-03 added openDoorsAndDraws parameter
2025-08-03 added function for angle of rear cupboard
2025-08-03 added sliding doors and door channels
2025-08-03 firxt commit
2025-08-03 Lots of updates - added 40mm duct and fans
2025-08-03 changed duct size
2025-08-03 added smaller duct size option
2025-08-03 updated fan calculations for thermal management
2025-08-21 work in progress
2025-08-29 First attempt at PCB design
2025-09-04 New SMD design
2025-09-04 Added footprints not in Kicad library
2025-09-04 Changed to high side relay drive and added 4.1V PS for high side relay hold
2025-09-10 Footprints and 3D models
2025-09-10 First attempt at PCB layout
2025-09-10 Fan duct design twin 40mm fans connected to standard 40mm PVC duct
2025-09-21 Close to final design
2025-09-21 Updated design to use BOSL2
2025-10-04 Re-organising directory structure
2025-10-06 Added optocouplers to flow sensors
2025-10-06 updated 4V1 switcher resistor values. Clean up and reannotate PCB
